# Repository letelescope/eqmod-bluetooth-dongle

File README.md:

# DIY EQMOD Bluetooth Dongle

This project demonstrates how to set a wireless Bluetooth connection for an EQMOD-compatible telescope mount using an HC-05 Bluetooth module. Optionally, the HC-05 module can be configured using AT command mode, allowing you to customize its settings such as name, password, and baud rate.

> All this is very much inspired of the official EQDirect-BT schematic available on the [EQMod website](https://eq-mod.sourceforge.net/eqdirectindex.html).

## Project Structure

```markdown
eqmod-bluetooth-dongle/
├── electronics/                  # Circuit diagrams and PCB layouts (to be added)
│   ├── eqmod-bluetooth-dongle/   # PCB design files for the EQMOD Bluetooth dongle
│   └── README.md                 # Explains the schematics and PCB layouts
│
├── utils/
│   └── flash-HC-05/              # PlatformIO project to configure HC-05 via AT commands using an Arduino board
│       ├── src/
│       │   └── main.cpp          # Arduino firmware code for HC-05 configuration
│       ├── platformio.ini        # PlatformIO configuration file
│       └── README.md             # Usage of the HC-05 configuration utility
│ 
├── LICENSE                       # Project license
└── README.md                     # You are here!
```

For the time being, this project only includes the utility to configure the HC-05 module. The main EQMOD Bluetooth dongle firmware will be added in the future.

## Configuring HC-05 Module via AT Commands

For configuring the HC-05 module, you can use the provided PlatformIO project located in the [utils/flash-HC-05/](utils/flash-HC-05/) directory. This project allows you to send AT commands to the HC-05 module using an Arduino board as a bridge. Please see the [readme](utils/flash-HC-05/README.md) file in that directory for detailed instructions. 

But basically, to configure the HC-05 module, you can follow these steps:

1. Connect and wire the HC-05 module to your Arduino board
2. Upload the provided firmware to your Arduino board using PlatformIO.
3. Open the Serial Monitor and send AT commands to the HC-05 module.
4. The module will respond to the commands, allowing you to configure its settings.

## Electronics schematics

The schematic diagrams and PCB layouts for the EQMOD Bluetooth dongle can be found in the [electronics/eqmod-bluetooth-dongle/](electronics/eqmod-bluetooth-dongle/) directory. Please refer to the [readme](electronics/eqmod-bluetooth-dongle/README.md) file in that directory for detailed explanations of the schematics and PCB layouts.

### TL;DR:

The EQMOD Bluetooth dongle is designed around the HC-05 Bluetooth module, which provides wireless serial communication capabilities. The schematic includes the necessary connections for power, ground, and serial communication (TX/RX) between the HC-05 module and the mount. The design also incorporates level shifting components to ensure compatibility between the HC-05 module's voltage levels and the mount's logic levels.

## Bibliography

- HC-05 Bluetooth Module Datasheet: [https://components101.com/sites/default/files/component_datasheet/HC-05%20Datasheet.pdf)](https://components101.com/sites/default/files/component_datasheet/HC-05%20Datasheet.pdf)
- EQMod EQDirect-BT documentation: [https://eq-mod.sourceforge.net/eqdirectindex.html](https://eq-mod.sourceforge.net/eqdirectindex.html)

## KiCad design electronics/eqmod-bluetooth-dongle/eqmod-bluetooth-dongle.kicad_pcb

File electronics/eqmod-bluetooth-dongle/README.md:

# EQMOD Bluetooth Dongle - Electronics

Schematic diagrams and PCB layouts for the EQMOD Bluetooth dongle can be found in the [electronics/eqmod-bluetooth-dongle/](electronics/eqmod-bluetooth-dongle/) directory.

## Project Files

```markdown
electronics/eqmod-bluetooth-dongle/
├── footprints/                             # Electronic footprint files
├── eqmod-bluetooth-dongle.kicad_pro        # PCB project file
├── eqmod-bluetooth-dongle.kicad_sch        # Schematic file
├── eqmod-bluetooth-dongle.kicad_pcb        # PCB layout file
├── eqmod-bluetooth-dongle.kicad_prl        # PCB rules file
└──README.md                                # This file
```

## Schematic principles

> All this is very much inspired of the official EQDirect-BT schematic available on the [EQMod website](https://eq-mod.sourceforge.net/eqdirectindex.html).

The EQMOD Bluetooth dongle is designed around the HC-05 Bluetooth module, which provides wireless serial communication capabilities. The schematic includes the necessary connections for power, ground, and serial communication (TX/RX) between the HC-05 module and the mount. The design also incorporates level shifting components to ensure compatibility between the HC-05 module's voltage levels and the mount's logic levels.

It consist of three sections:

- The Bluetooth module section: The HC-05 module and the associated logic level shifter to enable +5V TTL signaling with the Mount.
- The Power section: This provides stable voltages
  - +5V from the +12V Mount power supply, using a LM7805 linear voltage regulator.
  - +3.3V from the +5V line, using a voltage divider.
- The mount connection section: A simple generic 4-pin connector to connect to the EQMOD-compatible mount (via wiring to RJ45, RJ12 or DB9 connectors).

## PCB Layout

The PCB design implements the schematic, adhering to a straightforward routing strategy. This is a 4-layer PCB:

- Top Layer: Component placement and signal routing. With the exception of +12V routing from mount connector to the voltage regulator.
- Inner Layer 1: +5V power plane.
- Inner Layer 2: +3.3V power plane.
- Bottom Layer: Ground plane.

## Bibliography

- EQMod EQDirect-BT documentation: [https://eq-mod.sourceforge.net/eqdirectindex.html](https://eq-mod.sourceforge.net/eqdirectindex.html)

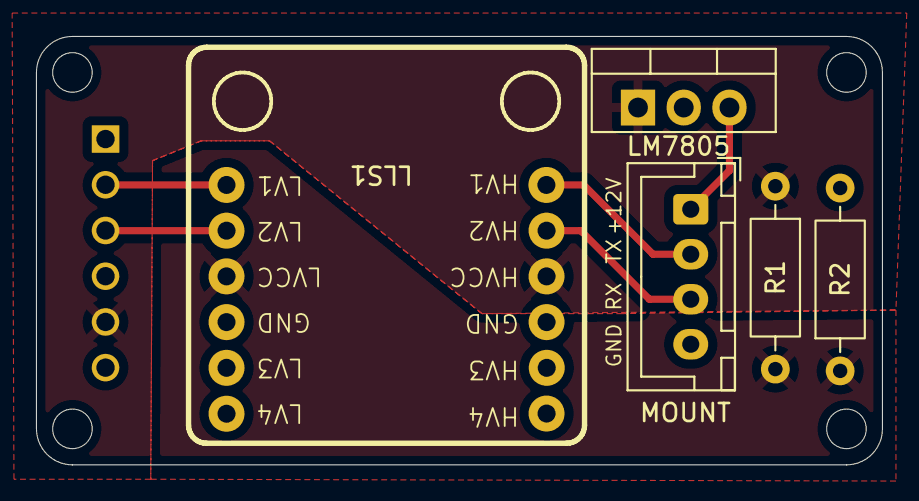
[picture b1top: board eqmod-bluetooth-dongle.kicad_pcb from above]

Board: 2 copper layers, 47.0 x 23.8 mm, 6 parts (1 on the bottom side), 8 nets.

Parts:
HC-05: ZC142200_HC-05-BT-Module; MODULE_ZC142200_HC05
LLS1: Logic_Level_Shifter; 333029_Logic_Level_Shifter
LM7805: LM7805_TO220; TO-220-3_Vertical
MOUNT: Mount; JST_XH_B4B-XH-A_1x04_P2.50mm_Vertical
R1: 4.7kΩ; R_Axial_DIN0207_L6.3mm_D2.5mm_P10.16mm_Horizontal
R2: 10kΩ; R_Axial_DIN0207_L6.3mm_D2.5mm_P10.16mm_Horizontal

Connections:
+3.3V: LLS1.10 (LVCC), R1.2, R2.1
+5V: HC-05.5 (VCC), LLS1.4 (HVCC), LM7805.1 (VI), R1.1
+12V: LM7805.3 (VO), MOUNT.1
GND: HC-05.4 (GND), LLS1.3 (GND), LLS1.9 (GND), LM7805.2 (GND), MOUNT.4, R2.2
MOUNT_RX: LLS1.5 (HV2), MOUNT.3
MOUNT_TX: LLS1.6 (HV1), MOUNT.2
unnamed: HC-05.2 (RX), LLS1.12 (LV1)
unnamed: HC-05.3 (TX), LLS1.11 (LV2)

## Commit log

2025-12-30 Init repository with HC-05 config utility
2025-12-30 Switch between AT and data mode
2025-12-30 Code snippet should be coherent with actual code
2025-12-30 fix: HC-05 flash util is not properly working (#1)
    * Read and write a line at a time
    * Switch between AT and data mode
2025-12-30 Kicad project init
2025-12-31 Minor util changes
2025-12-31 First schematic draft
2025-12-31 Schematics documentation
2025-12-31 feat: Kicad project init (#2)
    * Kicad project initialization
    * First schematics draft
    * Schematics documentation
    * Minor util fimware changes
2026-01-01 First PCB layout
2026-01-01 Documenting PCB layout
2026-01-02 Power planes
2026-01-02 With markings - ready to test
2026-01-02 New layout screenshot
2026-01-02 feat: Initiate PCB layout (#3)
    * Init PCB layout
    * With power planes
    * With markings
    * Documenting PCB layout
    * First test ready
2026-01-02 4-layer PCB and documentation
2026-01-02 feat: 4-layer PCB (#4)
    * 4-layer PCB routing
    * Documentation update
2026-01-02 Change mount connector to standard JST connector
2026-01-02 feat: standard JST connector (#5)
    * Change mount connector to standard JST connector
2026-01-04 Use connector that can be sourced from supplier
2026-01-05 Fix: Use connector that can be sourced from supplier (#6)
2026-01-10 Let's go print some PCB
2026-01-10 Let's go print some PCB (#7)
